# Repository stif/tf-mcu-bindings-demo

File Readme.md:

## Tinkerforge C/C++ Bindings for MCU (Demo)

The C/C++ bindings for microcontrollers allow you to control Tinkerforge [Bricks](https://www.tinkerforge.com/de/doc/Hardware/Bricks/Bricks.html) and
[Bricklets](https://www.tinkerforge.com/de/doc/Hardware/Bricklets/Bricklets.html) from your C/C++ programs running on microcontrollers.

This Demo is using [PlatformIO](https://platformio.org/) for compiling your project and
uploading to the microcontroller.

### PlatformIO

#### Using this Repository

```
git clone https://github.com/stif/tf-mcu-bindings-demo.git
cd tf-mcu-bindings-demo/
git submodule init
git submodule update
```
#### Create your own Repository

 * Create a Initial PlatformIO Project via PIO Home
    * Enter a Project Name
    * Select ESP32 Board (eg Olimex ESP32-PoE)
    * choose location of project
 * open a terminal in root folder of the project, and type:
 ```
 git init
 git submodule add https://github.com/stif/tf-hal-arduino-esp32.git lib/hal-arduino-esp32
 git submodule add https://github.com/stif/tf-mcu-bindings.git lib/bindings
 ```

 ### ESP32 SPI Pin Mapping

|SPI	|MOSI	   |MISO	   |CLK	   |CS     |
|-----|--------|--------|--------|-------|
|VSPI	|GPIO 23	|GPIO 19	|GPIO 18	|GPIO 5 |
|HSPI	|GPIO 13	|GPIO 12	|GPIO 14	|GPIO 15|
|Custom|GPIO 13	|GPIO *36*	|GPIO 14	|GPIO 15|

|Mapping |Lolin32 |ESP32-PoE UEXT| ESP32-PoE HAT |HAT Zero   |
|--------|--------|---------|---------|-----------|
|MOSI    |GPIO 13 |GPIO 13  |GPIO  3  |PIN 19     |
|MISO    |GPIO 12 |GPIO 36  |GPIO  35 |PIN 21     |
|CLK     |GPIO 14 |GPIO 14  |GPIO  0  |PIN 23     |
|CS A    |GPIO 32 |GPIO 16  |GPIO  32 |PIN 13     |
|CS B    |GPIO 33 |GPIO 2   |GPIO  33 |PIN 16     |
|CS C    |GPIO 4  |GPIO 4   |GPIO  13 |PIN 18     |
|CS D    |GPIO 5  |GPIO 5   |GPIO  16 |PIN 15     |
|CS HAT  |GPIO 15 |GPIO 15  |GPIO  5  |PIN 22     |

### Official Documentation

For more information about the C/C++ bindings (including setup instructions)
go to:

 * https://www.tinkerforge.com/en/doc/Software/API_Bindings_uC.html (English)
 * https://www.tinkerforge.com/de/doc/Software/API_Bindings_uC.html (German)

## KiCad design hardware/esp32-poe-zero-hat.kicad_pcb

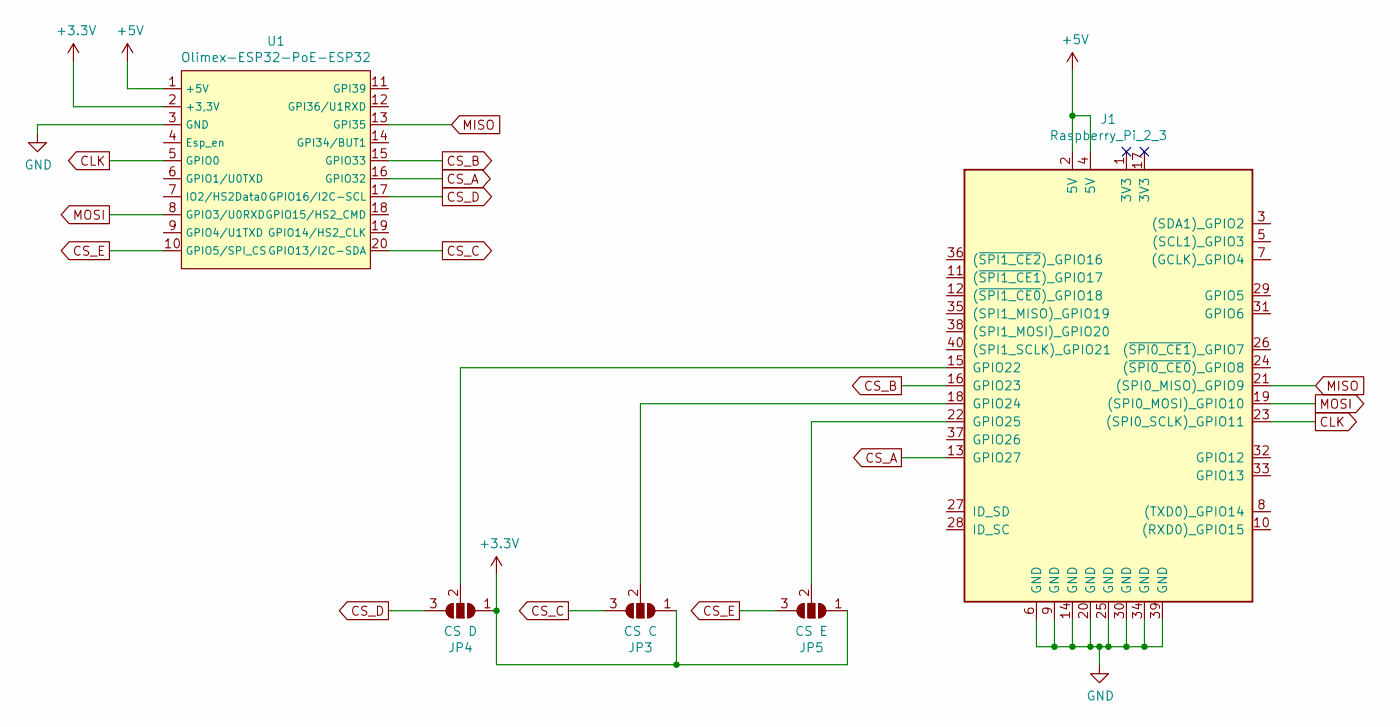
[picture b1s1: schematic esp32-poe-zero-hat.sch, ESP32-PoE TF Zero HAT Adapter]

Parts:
J1: Raspberry_Pi_2_3; PinHeader_2x20_P2.54mm_Vertical
JP3: CS C; SolderJumper-3_P1.3mm_Open_RoundedPad1.0x1.5mm
JP4: CS D; SolderJumper-3_P1.3mm_Open_RoundedPad1.0x1.5mm
JP5: CS E; SolderJumper-3_P1.3mm_Open_RoundedPad1.0x1.5mm
U1: Olimex-ESP32-PoE-ESP32; Olimex-ESP32-PoE

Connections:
+3V3: JP3.1 (A), JP4.1 (A), JP5.1 (A), U1.2 (+3,3V)
+5V: J1.2 (5V), J1.4 (5V), U1.1 (+5V)
CLK: J1.23 ((SPI0_SCLK)_GPIO11), U1.5 (GPIO0)
CS_A: J1.13 (GPIO27), U1.16 (GPIO32)
CS_B: J1.16 (GPIO23), U1.15 (GPIO33)
CS_C: JP3.3 (B), U1.20 (GPIO13/I2C-SDA)
CS_D: JP4.3 (B), U1.17 (GPIO16/I2C-SCL)
CS_E: JP5.3 (B), U1.10 (GPIO5/SPI_CS)
GND: J1.6 (GND), J1.9 (GND), J1.14 (GND), J1.20 (GND), J1.25 (GND), J1.30 (GND), J1.34 (GND), J1.39 (GND), U1.3 (GND)
MISO: J1.21 ((SPI0_MISO)_GPIO9), U1.13 (GPI35)
MOSI: J1.19 ((SPI0_MOSI)_GPIO10), U1.8 (GPIO3/U0RXD)
unnamed: J1.15 (GPIO22), JP4.2 (C)
unnamed: J1.18 (GPIO24), JP3.2 (C)
unnamed: J1.22 (GPIO25), JP5.2 (C)

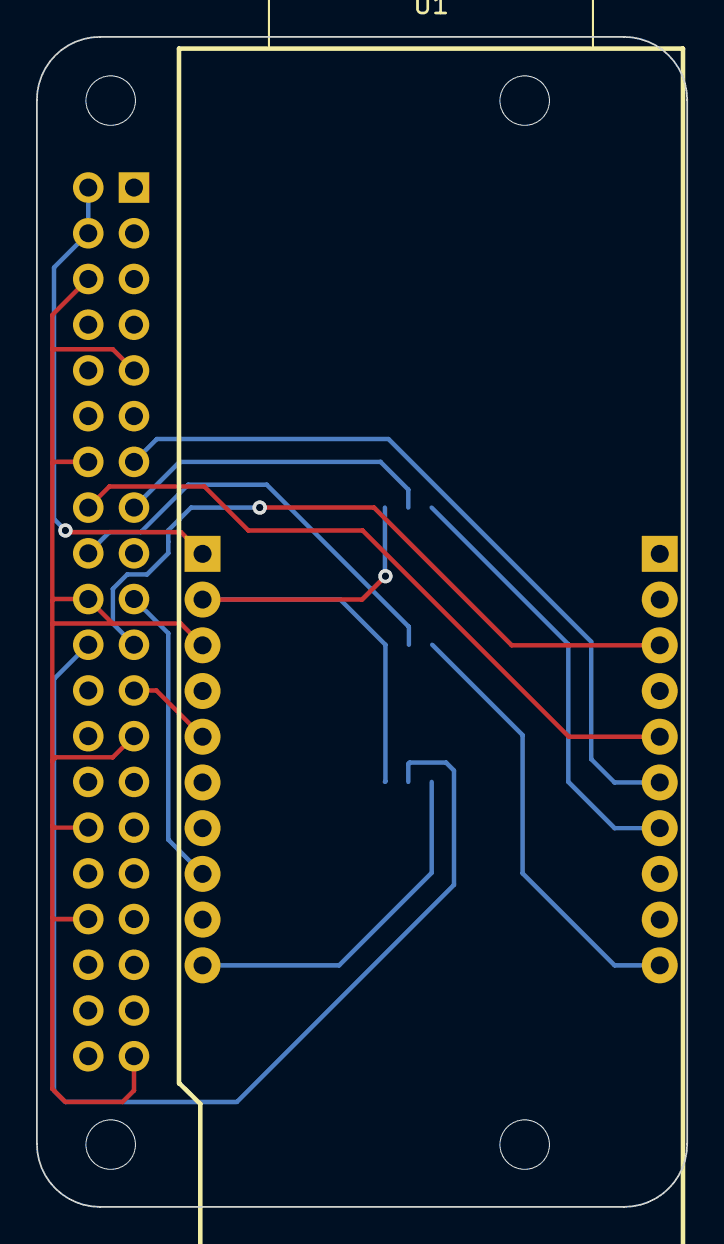
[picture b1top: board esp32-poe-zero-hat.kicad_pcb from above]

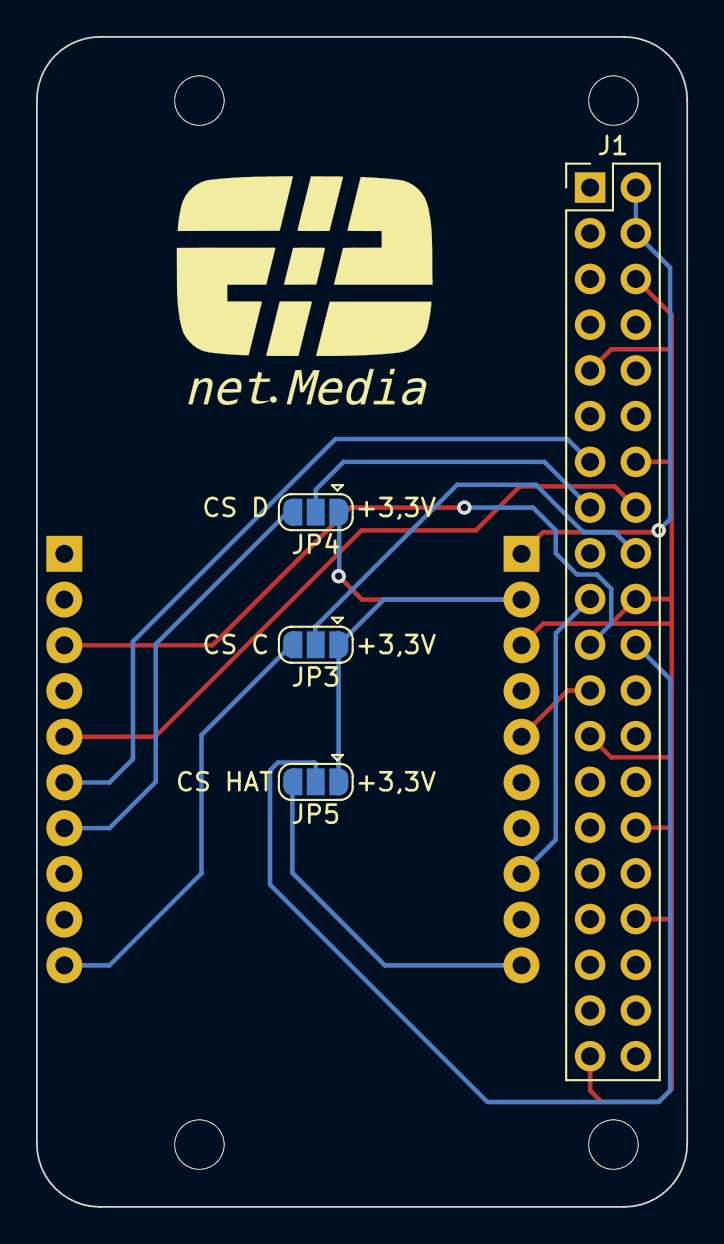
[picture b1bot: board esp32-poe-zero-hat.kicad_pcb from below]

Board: 2 copper layers, 36.1 x 65.0 mm, 6 parts (5 on the bottom side), 14 nets.

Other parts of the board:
J102: Raspberry_Pi_Zero; raspberrypi_zero_hat

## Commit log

2021-08-18 mapped SPI Pins and editing Ports
2021-08-18 added "getDeviceInfo"
2021-08-18 added Foto of Hardware Setup
2021-08-18 corrected Picture Link
2021-08-19 add Lolin32
2021-08-19 simplified main.cpp and updated hal-arduino-esp32
2021-08-20 added createTraffic() function
2021-08-20 deleted unused ports (important!)
2021-08-30 added Industrial Analog In
2021-08-30 added Industrial Analog Out
2021-08-30 added PTC V2 Bricklet
2021-08-30 modified main.cpp, hat_zero and thermocouple
2021-08-30 tested tf_utils for diagnositc functions (not working..)
2021-08-30 updated Readme to reflect new SPI Pins
2021-08-30 updated binding (industrial ptc)
2021-08-30 rename UID to prevent mix ups
2021-08-30 changed to *.cpp for correct linking
2021-08-31 put callback values in global variables
2021-09-20 remapped SPI to free Pins on UEXT Connector
2021-09-20 added tf_ind_relais_dual
2021-09-20 added KiCad Files for ESP-PoE to Hat Zero Adapter
2021-09-20 added dual ac relais and updated binding submodule
